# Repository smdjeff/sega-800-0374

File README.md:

# sega-800-0374
Working reproduction of Sega G80 800-0374

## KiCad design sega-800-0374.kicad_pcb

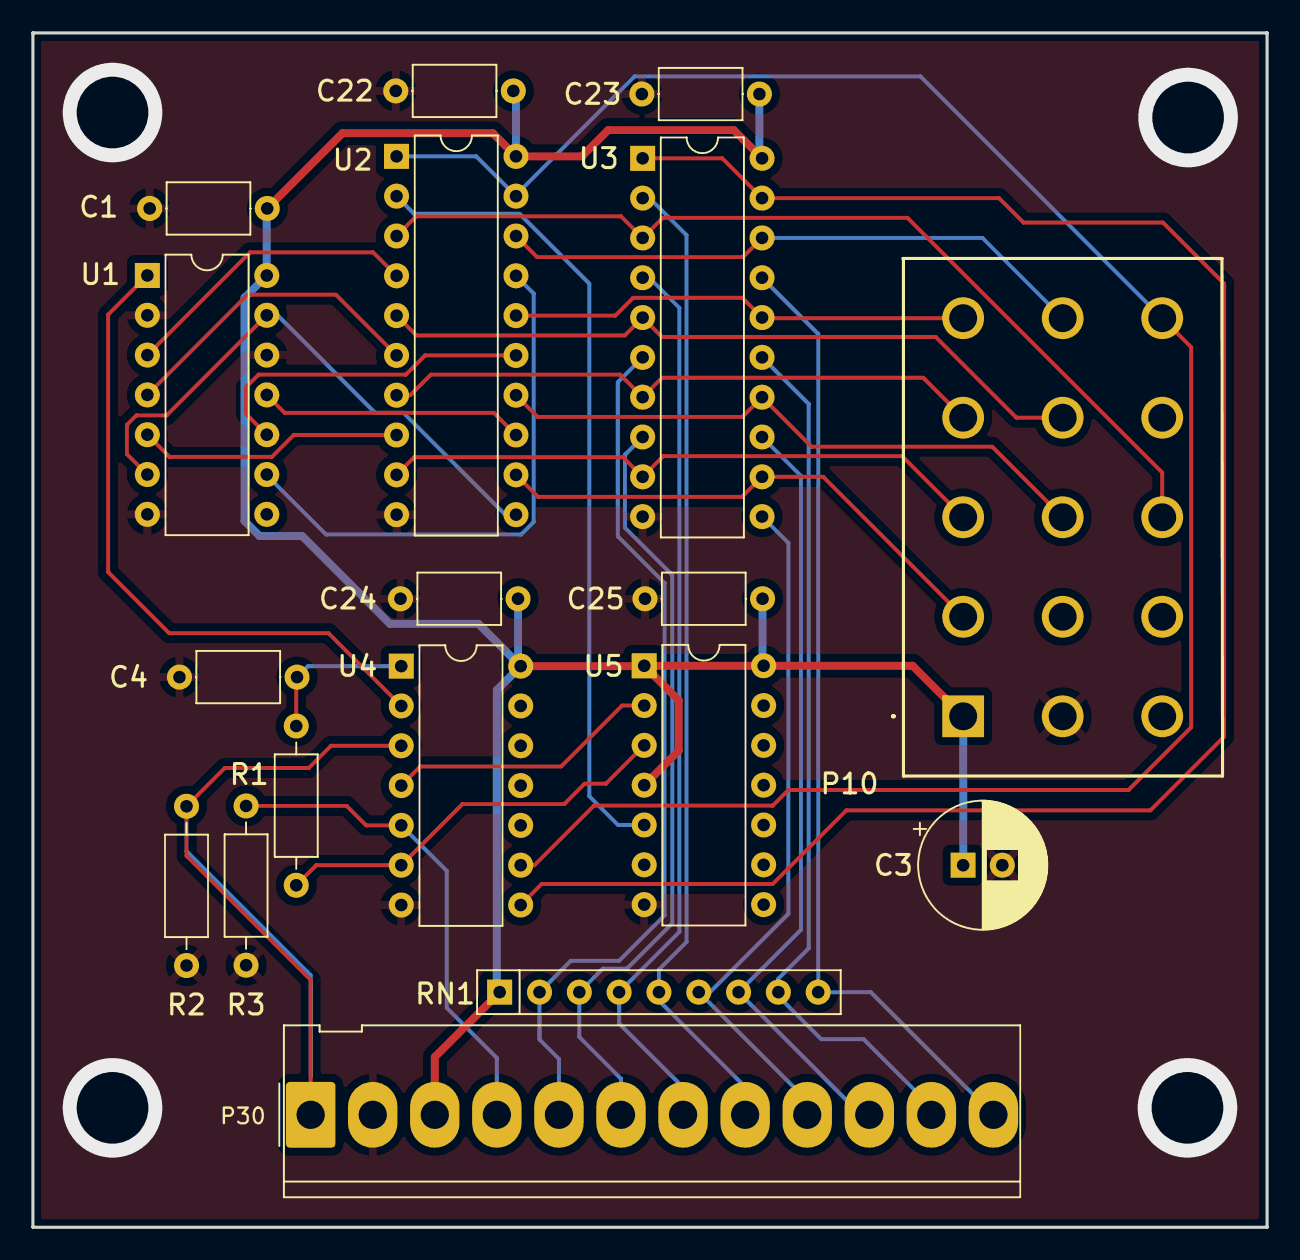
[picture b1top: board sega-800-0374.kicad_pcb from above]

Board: 2 copper layers, 78.7 x 76.2 mm, 18 parts (0 on the bottom side), 33 nets.

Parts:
C1, C22, C23, C24, C25: .01uF 16v; C_Axial_L5.1mm_D3.1mm_P7.50mm_Horizontal
C3: 10uF 25v; CP_Radial_D8.0mm_P2.50mm
C4: .001uF 16v; C_Axial_L5.1mm_D3.1mm_P7.50mm_Horizontal
P10: 0010844152
P30: Conn_01x12_Male; Molex_KK-396_5273-12A_1x12_P3.96mm_Vertical
R1, R2, R3: 1k 1/2w; R_Axial_DIN0207_L6.3mm_D2.5mm_P10.16mm_Horizontal
RN1: 2.2k; R_Array_SIP9
U1: 74LS393; DIP-14_W7.62mm
U2, U3: 74LS244; DIP-20_W7.62mm
U4: 74LS14; DIP-14_W7.62mm
U5: 74LS74; DIP-14_W7.62mm

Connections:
+5V: C1.1, C3.1, C22.1, C23.1, C24.1, C25.1, P10.1, P30.3, RN1.1 (common), U1.14 (VCC), U2.20 (VCC), U3.20 (VCC), U4.14 (VCC), U5.1 (~R), U5.4 (~S), U5.14 (VCC)
/B0: P10.14, U2.18 (O0a), U3.18 (O0a)
/B1: P10.13, U2.16 (O1a), U3.16 (O1a)
/B2: P10.8, U2.14 (O2a), U3.14 (O2a)
/B3: P10.4, U2.12 (O3a), U3.12 (O3a)
/B4: P10.7, U2.9 (O0b), U3.9 (O0b)
/B5: P10.10, U2.7 (O1b), U3.7 (O1b)
/B6: P10.11, U2.5 (O2b), U3.5 (O2b)
/B7: P10.9, U2.3 (O3b), U3.3 (O3b)
/IN0: P30.6, RN1.3 (R2), U3.8 (I3a)
/IN1: P30.5, RN1.2 (R1), U3.6 (I2a)
/IN2: P30.8, RN1.5 (R4), U3.2 (I0a)
/IN3: P30.7, RN1.4 (R3), U3.4 (I1a)
/IN4: P30.9, RN1.6 (R5), U3.11 (I0b)
/IN5: P30.10, RN1.7 (R6), U3.13 (I1b)
/IN6: P30.11, RN1.8 (R7), U3.15 (I2b)
/IN7: P30.12, RN1.9 (R8), U3.17 (I3b)
/OUT0: P10.15, U2.1 (OEa), U2.19 (OEb), U4.9
/Q0: U1.3 (Q0), U2.4 (I1a)
/Q1: U1.4 (Q1), U2.6 (I2a)
/Q2: U1.5 (Q2), U2.8 (I3a)
/Q3: U1.6 (Q3), U1.13 (CP), U2.11 (I0b)
/Q4: U1.11 (Q0), U2.13 (I1b)
/Q5: U1.10 (Q1), U2.15 (I2b)
/Q6: U1.9 (Q2), U2.17 (I3b)
/SPIN_C: R1.1, U4.6, U5.3 (C)
/SPIN_CLK: P30.4, R3.2, U4.5
/SPIN_DIR: P30.1, R2.2, U4.3
/SPIN_Q: U2.2 (I0a), U5.5 (Q)
GND: C1.2, C3.2, C4.2, C22.2, C23.2, C24.2, C25.2, P10.2, P30.2, R2.1, R3.1, U1.2 (MR), U1.7 (GND), U1.12 (MR), U2.10 (GND), U3.10 (GND), U4.7 (GND), U5.7 (GND)
unnamed: U1.1 (CP), U4.2
unnamed: U3.1 (OEa), U3.19 (OEb), U4.8
unnamed: U4.4, U5.2 (D)
